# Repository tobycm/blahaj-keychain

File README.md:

# Blahaj Keychain

with glow-in-the-dark eye, purrfect for presents :3

## Schematic

## PCB

## Features
- stay-on LED after pressing the button
- glow-in-the-dark eye
- shiny body
- very cute

## BOM

| Part           | Value   | Quantity |
|:---------------|:--------|---------:|
| Resistor       | 4.7k    |        1 |
| Resistor       | 220     |        6 |
| Photoresistor  |         |        1 |
| LED            |         |        2 |
| Capacitor      | 10uF    |        1 |
| 2N3904         |         |        2 |
| 2N3906         |         |        1 |
| Battery Holder |         |        1 |
| Button         |         |        1 |

made by the one and only [@tobycm](https://github.com/tobycm) :3 rawrrrr

readme ~~copied~~ inspired from [https://github.com/cheyao/Open555](https://github.com/cheyao/Open555)

design ur own pcb at [https://solder.hackclub.com](https://solder.hackclub.com)

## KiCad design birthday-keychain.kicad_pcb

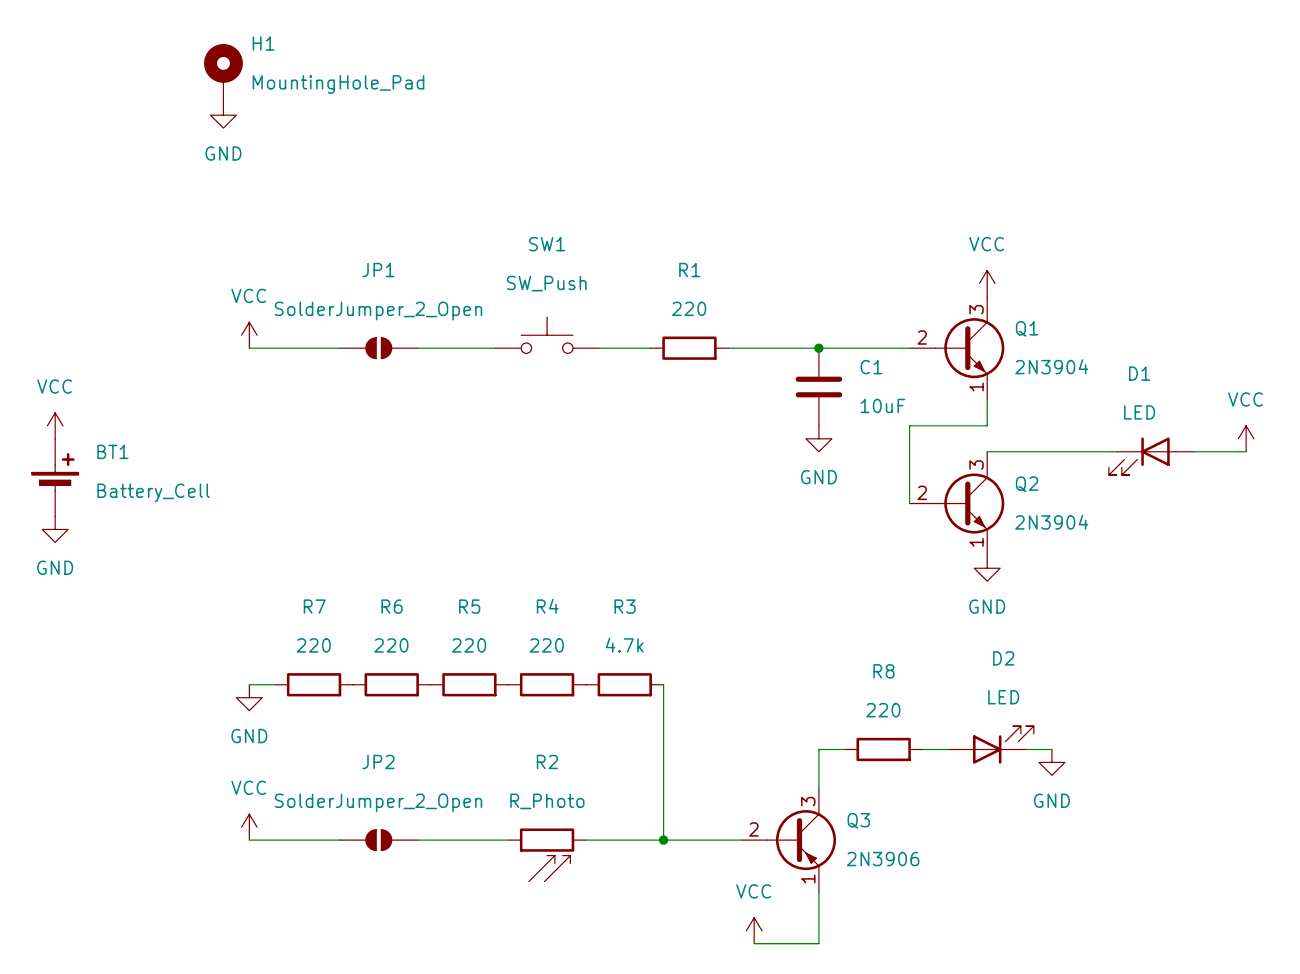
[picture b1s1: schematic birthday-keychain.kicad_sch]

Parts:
BT1: Battery_Cell; BatteryHolder_Keystone_3034_1x20mm
C1: 10uF; C_Disc_D7.5mm_W2.5mm_P5.00mm
D1, D2: LED; LED_D5.0mm
H1: MountingHole_Pad; MountingHole_3.2mm_M3_Pad
JP1, JP2: SolderJumper_2_Open; SolderJumper-2_P1.3mm_Open_TrianglePad1.0x1.5mm
Q1, Q2: 2N3904; TO-92_Inline
Q3: 2N3906; TO-92_Inline
R1, R4, R5, R6, R7, R8: 220; R_Axial_DIN0207_L6.3mm_D2.5mm_P7.62mm_Horizontal
R2: R_Photo; R_LDR_5.1x4.3mm_P3.4mm_Vertical
R3: 4.7k; R_Axial_DIN0207_L6.3mm_D2.5mm_P7.62mm_Horizontal
SW1: SW_Push; SW_PUSH_6mm

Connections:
GND: BT1.2 (-), C1.1, D2.1 (K), H1.1, Q2.1 (E), R7.1
unnamed: D1.1 (K), Q2.3 (C)
unnamed: D2.2 (A), R8.2
unnamed: JP1.2 (B), SW1.1
unnamed: JP2.2 (B), R2.1
unnamed: C1.2, Q1.2 (B), R1.2
unnamed: Q1.1 (E), Q2.2 (B)
unnamed: Q3.2 (B), R2.2, R3.2
unnamed: Q3.3 (C), R8.1
unnamed: R1.1, SW1.2
unnamed: R3.1, R4.2
unnamed: R4.1, R5.2
unnamed: R5.1, R6.2
unnamed: R6.1, R7.2
VCC: BT1.1 (+), D1.2 (A), JP1.1 (A), JP2.1 (A), Q1.3 (C), Q3.1 (E)

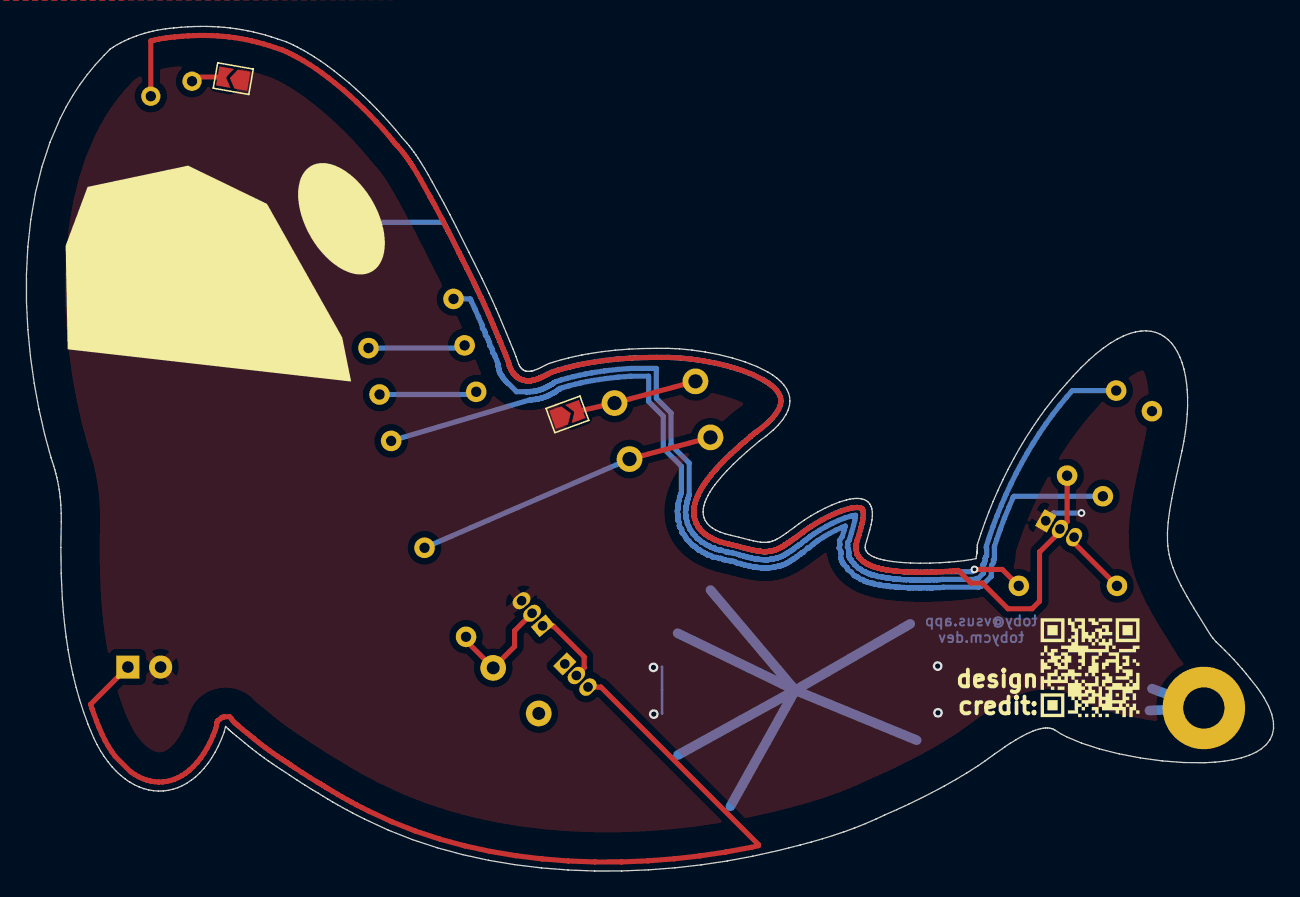
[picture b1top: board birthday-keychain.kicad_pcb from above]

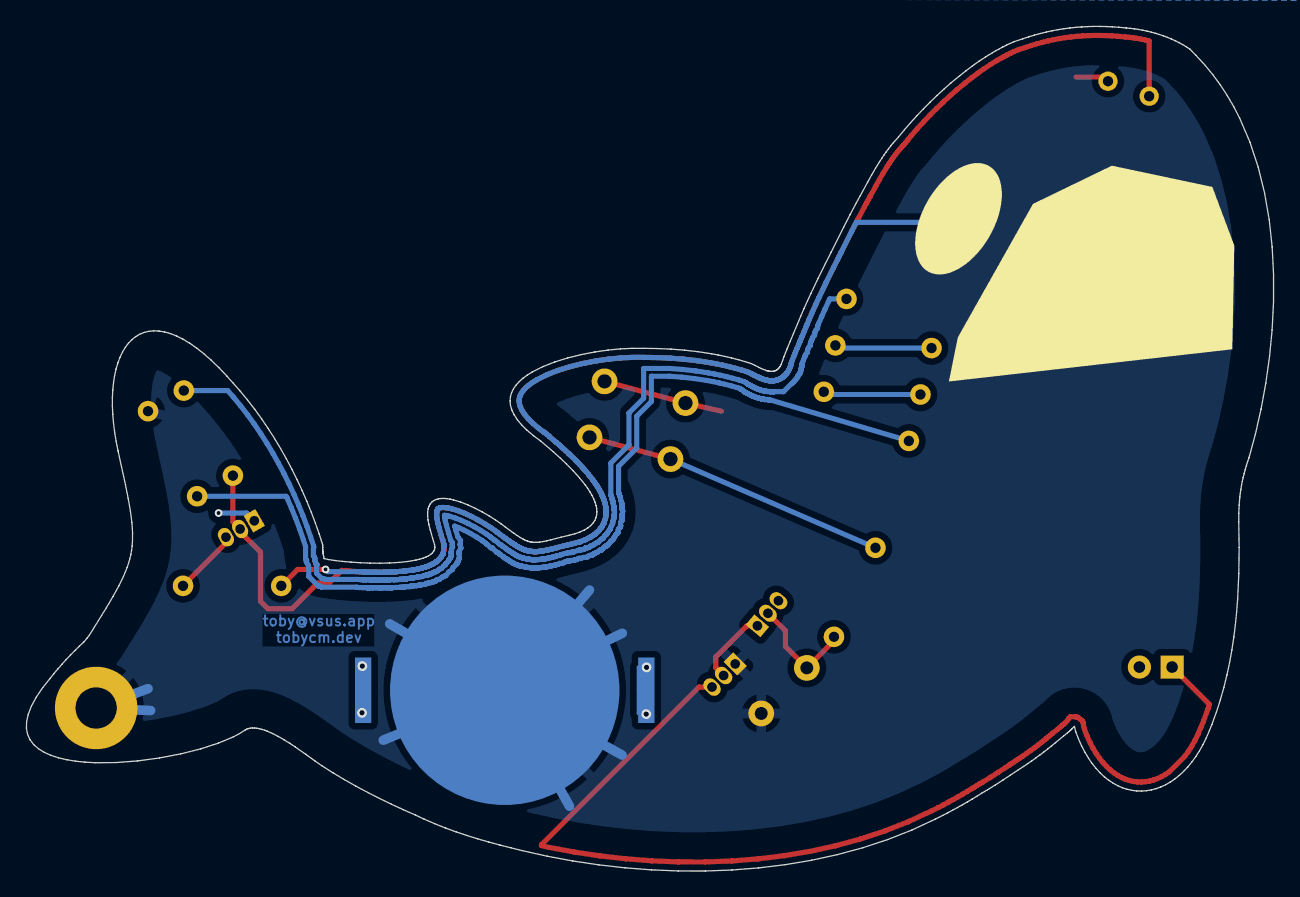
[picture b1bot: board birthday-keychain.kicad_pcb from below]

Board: 2 copper layers, 96.8 x 65.5 mm, 19 parts (10 on the bottom side), 15 nets.

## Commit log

2025-05-08 banger pcb
